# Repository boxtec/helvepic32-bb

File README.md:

# helvepic32-bb
HelvePic32 Breadboard

See http://helvepic32.net or http://helvepic32.org/ for more information.

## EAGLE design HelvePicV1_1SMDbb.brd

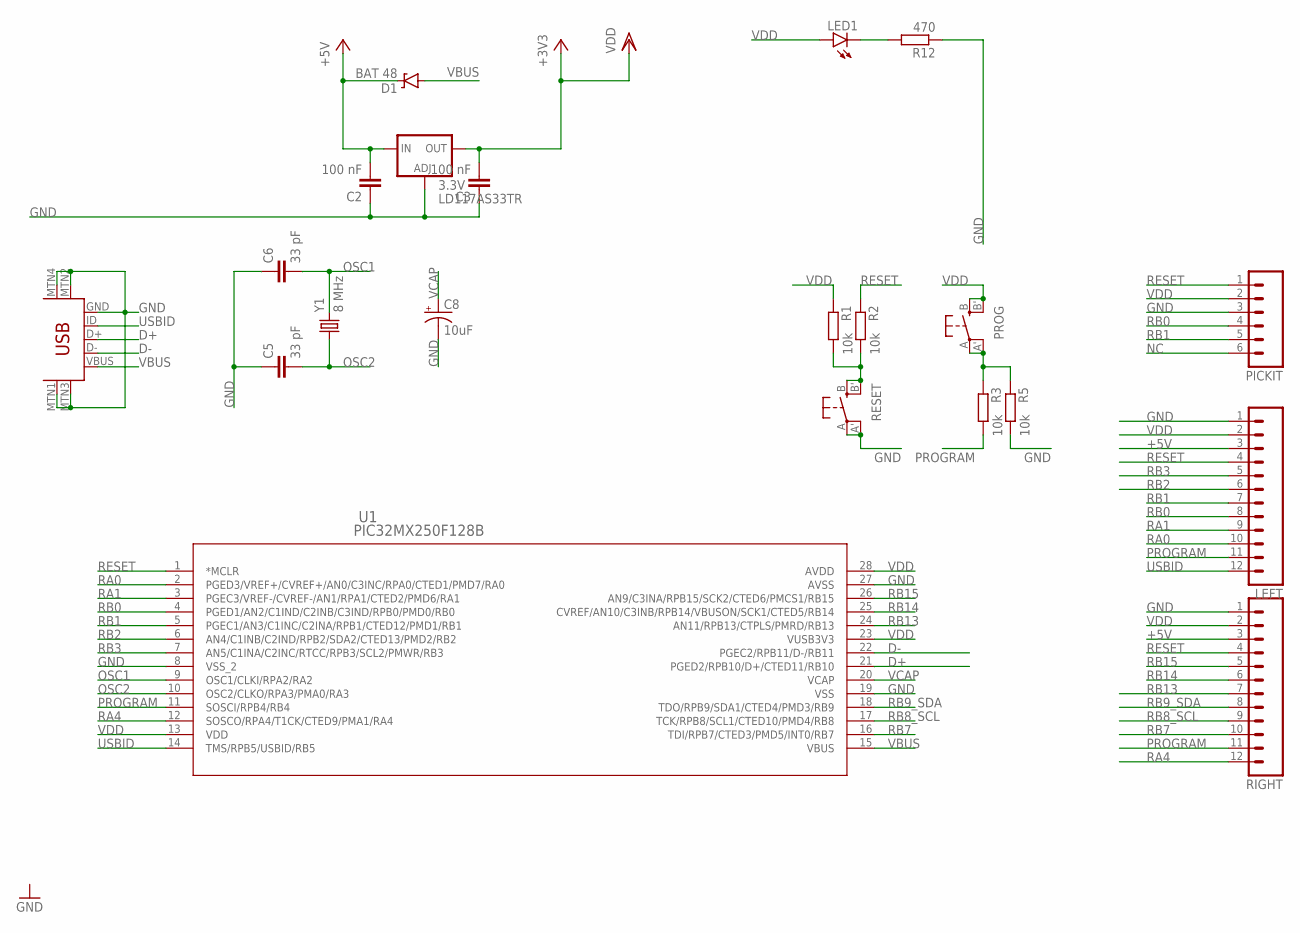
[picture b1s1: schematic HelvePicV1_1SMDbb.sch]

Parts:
3.3V: LD117AS33TR; SOT223
C2, C3: 100 nF; 0805
C5, C6: 33 pF; 0805
C8: 10uF; EIA3216
D1: BAT 48; SMB-DIODE
LED1: LED1206; LED-1206
LEFT: M12PTH; 1X12
PICKIT: M06LOCK; 1X06_LOCK
PROG: SPST_TACT-EVQQ2; EVQ-Q2
R1, R2, R3, R5: 10k; M0805
R12: 470; M0805
RESET: SPST_TACT-EVQQ2; EVQ-Q2
RIGHT: M12PTH; 1X12
U1: PIC32MX250F128B; SOIC28-W_MC
U$2: USB-MINIB-5PIN; USB-MINIB
Y1: 8 MHz; HC49UP

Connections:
+5V: 3.3V.3 (IN), C2.2, D1.C, LEFT.3, RIGHT.3
D+: U1.21 (PGED2/RPB10/D+/CTED11/RB10), U$2.D+
D-: U1.22 (PGEC2/RPB11/D-/RB11), U$2.D-
GND: 3.3V.1 (ADJ), C2.1, C3.1, C5.1, C6.1, C8.C (-), LEFT.1, PICKIT.3, R5.2, R12.1, RESET.A, RESET.A' (P1), RIGHT.1, U1.8 (VSS_2), U1.19 (VSS), U1.27 (AVSS), U$2.GND, U$2.MTN1 (MTN2), U$2.MTN2 (MTN3), U$2.MTN3 (MTN1), U$2.MTN4
unnamed: LED1.C, R12.2
unnamed: PROG.A, PROG.A' (P1), R3.1, R5.1
unnamed: R1.2, R2.2, RESET.B (S), RESET.B' (S1)
NC: PICKIT.6
OSC1: C6.2, U1.9 (OSC1/CLKI/RPA2/RA2), Y1.2
OSC2: C5.2, U1.10 (OSC2/CLKO/RPA3/PMA0/RA3), Y1.1
PROGRAM: LEFT.11, R3.2, RIGHT.11, U1.11 (SOSCI/RPB4/RB4)
RA0: LEFT.10, U1.2 (PGED3/VREF+/CVREF+/AN0/C3INC/RPA0/CTED1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)
RA1: LEFT.9, U1.3 (PGEC3/VREF-/CVREF-/AN1/RPA1/CTED2/PMD6/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)
RA4: RIGHT.12, U1.12 (SOSCO/RPA4/T1CK/CTED9/PMA1/RA4)
RB0: LEFT.8, PICKIT.4, U1.4 (PGED1/AN2/C1IND/C2INB/C3IND/RPB0/PMD0/R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)
RB1: LEFT.7, PICKIT.5, U1.5 (PGEC1/AN3/C1INC/C2INA/RPB1/CTED12/PMD1/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)
RB2: LEFT.6, U1.6 (AN4/C1INB/C2IND/RPB2/SDA2/CTED13/PMD2/R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)
RB3: LEFT.5, U1.7 (AN5/C1INA/C2INC/RTCC/RPB3/SCL2/PMWR/RB3)
RB7: RIGHT.10, U1.16 (TDI/RPB7/CTED3/PMD5/INT0/RB7)
RB8_SCL: RIGHT.9, U1.17 (TCK/RPB8/SCL1/CTED10/PMD4/RB8)
RB9_SDA: RIGHT.8, U1.18 (TDO/RPB9/SDA1/CTED4/PMD3/RB9)
RB13: RIGHT.7, U1.24 (AN11/RPB13/CTPLS/PMRD/RB13)
RB14: RIGHT.6, U1.25 (CVREF/AN10/C3INB/RPB14/VBUSON/SCK1/CTED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)
RB15: RIGHT.5, U1.26 (AN9/C3INA/RPB15/SCK2/CTED6/PMCS1/RB15)
RESET: LEFT.4, PICKIT.1, R2.1, RIGHT.4, U1.1 (*MCLR)
USBID: LEFT.12, U1.14 (TMS/RPB5/USBID/RB5), U$2.ID
VBUS: D1.A, U1.15 (VBUS), U$2.VBUS
VCAP: C8.A (+), U1.20 (VCAP)
VDD: 3.3V.4 (OUT), C3.2, LED1.A, LEFT.2, PICKIT.2, PROG.B (S), PROG.B' (S1), R1.1, RIGHT.2, U1.13 (VDD), U1.23 (VUSB3V3), U1.28 (AVDD)

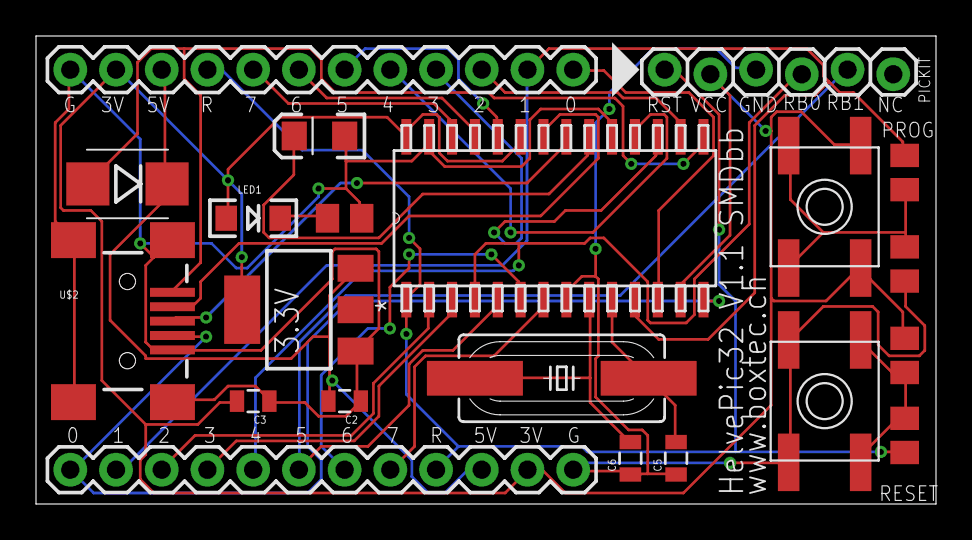
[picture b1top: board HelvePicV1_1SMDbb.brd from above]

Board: 2 copper layers, 50.0 x 26.0 mm, 21 parts (0 on the bottom side), 28 nets.

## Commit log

2015-12-09 Initial git import
2015-12-09 readme updated

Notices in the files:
parts and their libraries:
SparkFun-Capacitors: Licensing: Creative Commons ShareAlike 4.0 International - https://creativecommons.org/licenses/by-sa/4.0
